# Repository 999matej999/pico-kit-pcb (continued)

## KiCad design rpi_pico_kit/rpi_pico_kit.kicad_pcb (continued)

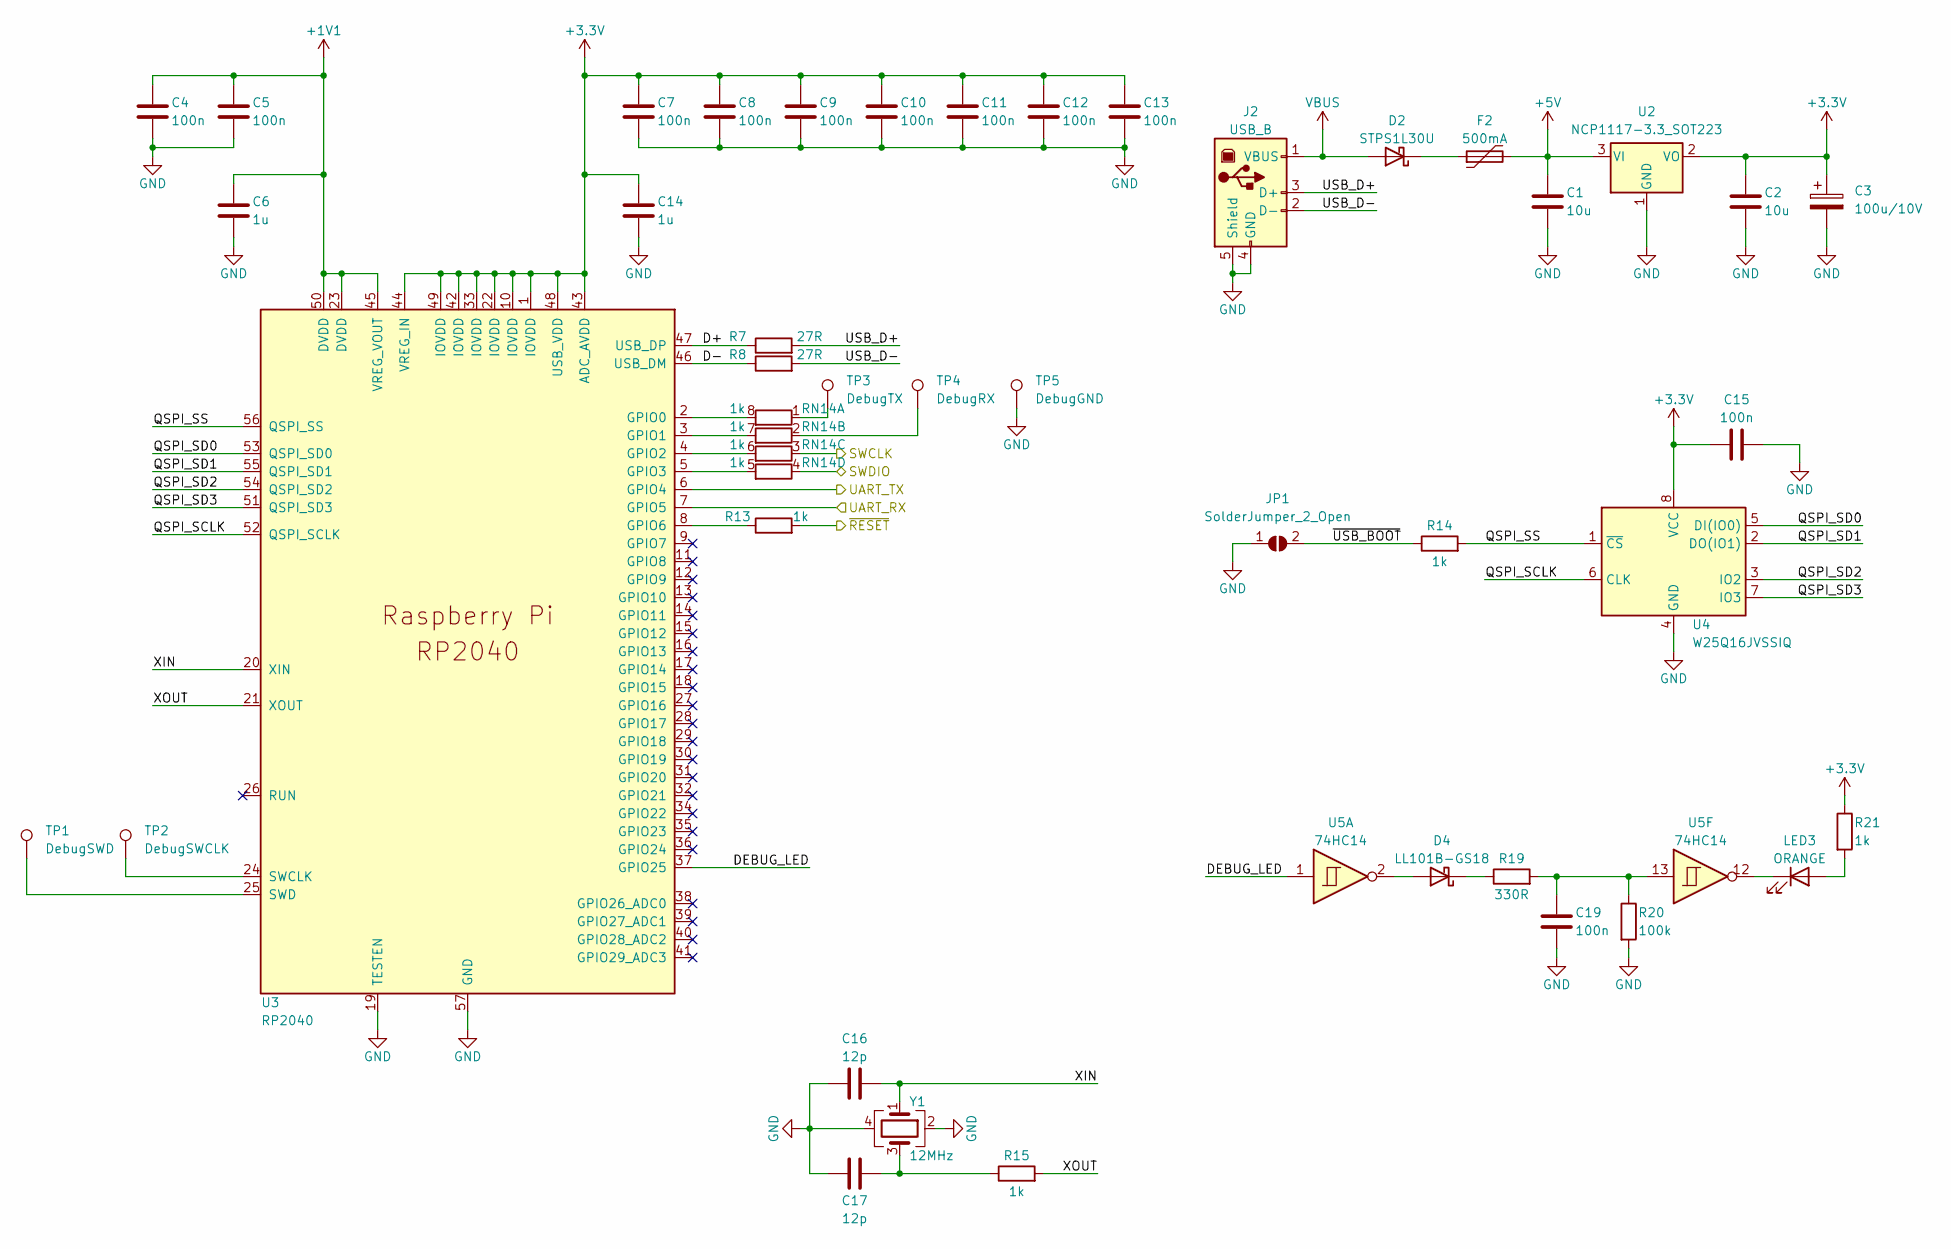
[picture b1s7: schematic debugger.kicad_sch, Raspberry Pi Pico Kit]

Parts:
C1, C2: 10u; C_0805_2012Metric_Pad1.18x1.45mm_HandSolder; Manufacturer Part Number CL21A106KOQNNNG
C3: 100u/10V; C_Elec_5x5.4; Manufacturer Part Number UWR1A101MCL1GB
C4, C5, C7, C8, C9, C10, C11, C12, C13, C15, C19: 100n; C_0603_1608Metric_Pad1.08x0.95mm_HandSolder; Manufacturer Part Number C0805C104M3RAC7800
C6, C14: 1u; C_0805_2012Metric_Pad1.18x1.45mm_HandSolder; Manufacturer Part Number C0805C105Z4VAC7800
C16, C17: 12p; C_0603_1608Metric_Pad1.08x0.95mm_HandSolder; Manufacturer Part Number C0805C120J1HAC7800
D2: STPS1L30U; D_SMB; Manufacturer Part Number STPS1L30U
D4: LL101B-GS18; D_MiniMELF; Manufacturer Part Number LL101B-GS18
F2: 500mA; Fuse_1206_3216Metric_Pad1.42x1.75mm_HandSolder; Manufacturer Part Number 0ZCJ0050FF2G
J2: USB_B; USB_B_Lumberg_2411_02_Horizontal; Manufacturer Part Number USB-B1HSW6
JP1: SolderJumper_2_Open; SolderJumper-2_P1.3mm_Open_RoundedPad1.0x1.5mm
LED3: ORANGE; LED_0805_2012Metric_Pad1.15x1.40mm_HandSolder; Manufacturer Part Number LTST-C170KFKT
R7, R8: 27R; R_0603_1608Metric_Pad0.98x0.95mm_HandSolder; Manufacturer Part Number RC0805FR-0727RL
R13, R14, R15, R21: 1k; R_0603_1608Metric_Pad0.98x0.95mm_HandSolder; Manufacturer Part Number RC0805FR-071KL
R19: 330R; R_0603_1608Metric_Pad0.98x0.95mm_HandSolder; Manufacturer Part Number RC0805FR-13330RL
R20: 100k; R_0603_1608Metric_Pad0.98x0.95mm_HandSolder; Manufacturer Part Number RC0805FR-07100KL
RN14: 1k; R_Array_Convex_4x0603
TP1: DebugSWD; TestPoint_Pad_D1.0mm
TP2: DebugSWCLK; TestPoint_Pad_D1.0mm
TP3: DebugTX; TestPoint_Pad_D1.0mm
TP4: DebugRX; TestPoint_Pad_D1.0mm
TP5: DebugGND; TestPoint_Pad_D1.0mm
U2: NCP1117-3.3_SOT223; SOT-223-3_TabPin2; Manufacturer Part Number NCP1117ST33T3G
U3: RP2040; RP2040-QFN-56; Manufacturer Part Number SC0914(13)
U4: W25Q16JVSSIQ; SOIC-8_5.275x5.275mm_P1.27mm; Manufacturer Part Number W25Q16JVSSIQ
U5: 74HC14; SOIC-14_3.9x8.7mm_P1.27mm; Manufacturer Part Number 74HC14S14-13
Y1: 12MHz; Crystal_SMD_0603-4Pin_6.0x3.5mm; Manufacturer Part Number ABM3B-12.000MHZ-10-1-U-T

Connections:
+1V1: C4.2, C5.2, C6.2, U3.23 (DVDD), U3.45 (VREG_VOUT), U3.50 (DVDD)
+3V3: C2.2, C3.1, C7.2, C8.2, C9.2, C10.2, C11.2, C12.2, C13.2, C14.2, C15.1, R21.1, U2.2 (VO), U3.1 (IOVDD), U3.10 (IOVDD), U3.22 (IOVDD), U3.33 (IOVDD), U3.42 (IOVDD), U3.43 (ADC_AVDD), U3.44 (VREG_IN), U3.48 (USB_VDD), U3.49 (IOVDD), U4.8 (VCC); also elsewhere on the board
+5V: C1.2, F2.2, U2.3 (VI); also elsewhere on the board
/DEBUGGER_RX: U3.6 (GPIO4); also elsewhere on the board
/DEBUGGER_TX: U3.7 (GPIO5); also elsewhere on the board
/Debugger/D+: R7.1, U3.47 (USB_DP)
/Debugger/D-: R8.1, U3.46 (USB_DM)
/Debugger/DEBUG_LED: U3.37 (GPIO25), U5.1
/Debugger/QSPI_SCLK: U3.52 (QSPI_SCLK), U4.6 (CLK)
/Debugger/QSPI_SD0: U3.53 (QSPI_SD0), U4.5 (DI(IO0))
/Debugger/QSPI_SD1: U3.55 (QSPI_SD1), U4.2 (DO(IO1))
/Debugger/QSPI_SD2: U3.54 (QSPI_SD2), U4.3 (IO2)
/Debugger/QSPI_SD3: U3.51 (QSPI_SD3), U4.7 (IO3)
/Debugger/QSPI_SS: R14.2, U3.56 (QSPI_SS), U4.1 (~CS)
/Debugger/USB_D+: J2.3 (D+), R7.2
/Debugger/USB_D-: J2.2 (D-), R8.2
/Debugger/XIN: C16.2, U3.20 (XIN), Y1.1
/Debugger/XOUT: R15.2, U3.21 (XOUT)
/Debugger/~USB_BOOT: JP1.2 (B), R14.1
/SWCLK: RN14.3 (R3.1); also elsewhere on the board
/SWDIO: RN14.4 (R4.1); also elsewhere on the board
/~RESET: R13.2; also elsewhere on the board
GND: C1.1, C2.1, C3.2, C4.1, C5.1, C6.1, C7.1, C8.1, C9.1, C10.1, C11.1, C12.1, C13.1, C14.1, C15.2, C16.1, C17.1, C19.1, J2.4 (GND), J2.5 (Shield), JP1.1 (A), R20.2, TP5.1, U2.1 (GND), U3.19 (TESTEN), U3.57 (GND), U4.4 (GND), Y1.2, Y1.4; also elsewhere on the board
unnamed: C17.2, R15.1, Y1.3
unnamed: C19.2, R19.2, R20.1, U5.13
unnamed: D2.1 (K), F2.1
unnamed: D4.2 (A), U5.2
unnamed: D4.1 (K), R19.1
unnamed: LED3.2 (A), R21.2
unnamed: LED3.1 (K), U5.12
unnamed: RN14.1 (R1.1), TP3.1
unnamed: RN14.8 (R1.2), U3.2 (GPIO0)
unnamed: RN14.2 (R2.1), TP4.1
unnamed: RN14.7 (R2.2), U3.3 (GPIO1)
unnamed: RN14.6 (R3.2), U3.4 (GPIO2)
unnamed: RN14.5 (R4.2), U3.5 (GPIO3)
unnamed: R13.1, U3.8 (GPIO6)
unnamed: TP2.1, U3.24 (SWCLK)
unnamed: TP1.1, U3.25 (SWD)
VBUS: D2.2 (A), J2.1 (VBUS)

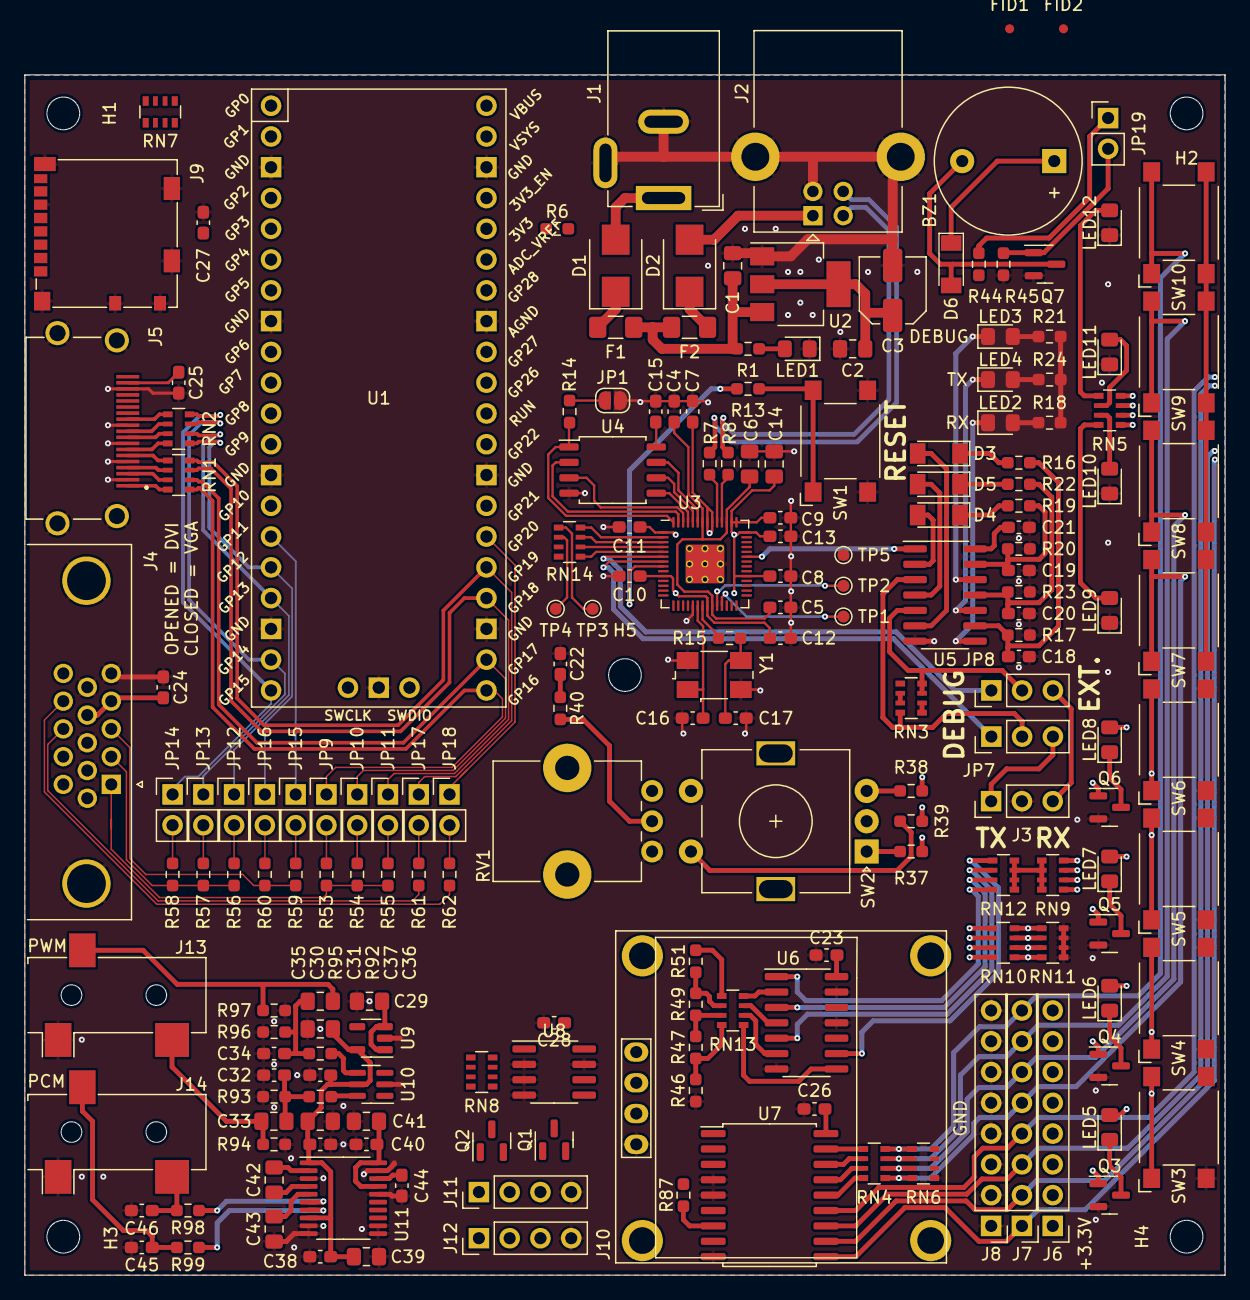
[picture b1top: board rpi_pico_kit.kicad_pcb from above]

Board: 4 copper layers, 99.1 x 99.1 mm, 196 parts (0 on the bottom side), 175 nets.

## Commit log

2022-01-17 added .gitignore file
2022-01-17 added kicad v6 project
2022-01-17 added second rpi pico as debugger
2022-01-17 added pinout for rpi pico
2022-01-17 added kit pinout
2022-01-17 added another components to schematic
2022-01-18 little changes
2022-01-18 moved dac buttons to hierarchical sheet
2022-01-18 removed dac buttons
2022-01-18 added SPI devices
2022-01-18 added i2c and audio interface
2022-01-18 added leds for uart, little changes
2022-01-18 edited debugger
2022-01-18 edited debugger, little changes
2022-01-18 edited pinout
2022-01-18 renamed parts, added footprints
2022-01-23 little changes, added EEPROM
2022-01-23 added jumper for 74165's MISO pin
2022-02-28 updated kicad version from 20211123 to 20220126
2022-03-06 added i2c interface for vga and dvi
2022-03-06 added uart selector
2022-03-06 added some footprints
2022-03-06 added dac buttons
2022-03-07 replaced spi expander
2022-03-07 replaced buttons in schematic
2022-03-07 added resistors to expander's buttons
2022-03-07 added i2c level shifters
2022-03-12 connected unused logic gates to ground
2022-03-16 added bypass capacitor to schmitt inverter
2022-03-17 changed schematic for uart leds
2022-03-18 added jumpers to vga
2022-03-18 changed pinout
2022-03-18 changed transistors to unused gates of 7414
2022-03-18 added test pads for uart and swd of debugger
2022-03-18 changed encoder button pull-up to pull-down
2022-03-18 added some MPNs, added fiducials
2022-03-19 edited 5V I2C, added some footprints, MPNs, added HDMI footprint library
2022-03-19 added some footprints and MPNs
2022-03-19 added MPNs for capacitors
2022-03-19 added MPNs for resistors
2022-03-19 added another MPNs, edited color of LEDs
2022-03-19 added monostable for debug led
2022-03-19 changed back 7414 gates to mosfets
2022-03-19 added missing MPNs to edited parts
2022-03-19 changed name of LEDs from D to LED
2022-03-19 added MPNs
2022-03-19 added micro sd footprint and MPN
2022-03-19 added protective diode to buzzer
2022-03-19 added SSD1306 library
2022-03-19 migrated library SSD1306, added footprint
2022-03-19 changed numbering of parts
2022-03-20 added solder jumpers to swd, changed numbering of parts
2022-03-20 changed uart pin headers to jumpers
2022-03-20 added PTC fuses
2022-03-20 added empty pcb file
2022-03-20 added parts to pcb
2022-03-20 added some 3D models
2022-03-20 changed switches from tht to smd
2022-03-20 changed footprint for tactile switches, added 3D model
2022-03-20 changed tactile switch 3D model
2022-03-20 added 3D models, repaired SSD1306 footprint
2022-03-20 added sim card 3D model
2022-03-20 changed footprint for flash memory
2022-03-20 added USB B 3D model
2022-03-20 changed footprint for crystal
2022-03-20 added OLED socket
2022-03-20 added RPi Pico socket
2022-03-20 repaired switch 3D model
2022-03-21 added JumperTHT library
2022-03-21 renamed files of JumperTHT library
2022-03-21 changed footprint for THT jumpers to use jumper 3D model
2022-03-21 changed RV1 3D model
2022-03-21 changed potentiometer footprint
2022-03-21 edited board setup
2022-03-21 edited mask clearance
2022-03-21 created Custom library with custom SMD button switch
2022-03-21 updated kicad version from 20220211 to 20220308
2022-03-21 edited OLED footprint
2022-03-21 removed additional holes for oled
2022-03-21 initial changes in pcb, drawn pcb outline
2022-03-21 filtered controls and indicators
2022-03-21 changed position of controls and indicators
2022-03-21 added rpi pico THT and SMD footprint
2022-03-21 edited RPi Pico SMD and THT footprint
2022-03-21 edited RPi Pico THT library
2022-03-21 changed rpi pico footprint in project
2022-03-21 pcb changes
2022-03-22 changed resistors to resistor arrays
2022-03-22 added footprints for resistor arrays
2022-03-22 added missing footprints
2022-03-22 downgraded kicad version from 20220308 to 20220211
2022-03-22 added resistor arrays to pcb
2022-03-22 changed footprints from 0805 to 0603
2022-03-22 changed footprint U10
2022-03-22 SPI conflict solved
2022-03-22 changed footprint for diodes
2022-03-22 rearranged parts to blocks
2022-03-22 added RPi Pico THT socket footprint
2022-03-22 added RPi Pico THT socket 3D model
2022-03-22 changed RPi Pico footprint in pcb
2022-03-22 changed footprints for resistor arrays
2022-03-22 added names to differential pairs
2022-03-22 updated pcb netlist
2022-03-22 added net classes
2022-03-24 replaced audio
2022-03-24 4 layer stackup
2022-03-24 edited layer thickness
2022-03-25 added permitivity of JLC 7628 stackup
2022-03-25 edited thickness of prepregs layers
2022-03-25 added differential dvi lines (unrouted 523)
2022-03-25 edited impedance controller tracks parameters (unrouted 534)
2022-03-25 added GND filed zones (unrouted 421)
2022-03-25 added nets to vga class
2022-03-25 vga (unrouted 401)
2022-03-25 vga (unrouted 389)
2022-03-25 updated GND plane
2022-03-25 moved text
2022-03-25 changed eeprom I2C address from 0x50 to 0x51
2022-03-26 solved some DRC errors
2022-03-26 audio (unrouted 353)
2022-03-26 added GND vias to audio
2022-03-26 spi (unrouted 319)
2022-03-26 edited VGA tracks width
2022-03-26 basic leds (unrouted 295)
2022-03-26 dac buttons (unrouted 270)
2022-03-26 updated GND plane (unrouted 262)
2022-03-26 potentiomete, encoder (unrouted 257)
2022-03-26 expander (unrouted 234)
2022-03-26 added 5th hole at the center
2022-03-27 buzzer (unrouted 226)
2022-03-27 power (unrouted 221)
2022-03-27 power (unrouted 209)
2022-03-27 moved debugger (unrouted 190)
2022-03-27 debugger (unrouted 171)
2022-03-27 debugger (unrouted 163)
2022-03-27 debugger (unrouted 159)
2022-03-27 crystal (unrouted 155)
2022-03-27 little changes (unrouted 153)
2022-03-27 reset, test pads (unrouted 139)
2022-03-27 monostable (unrouted 136)
2022-03-27 monostable
2022-03-27 monostable (unrouted 115)
2022-03-27 monostable (unrouted 112)
2022-03-27 monostable (unrouted 105)
2022-03-27 little changes (unrouted 104)
2022-03-28 solved some errors and warnings
2022-03-28 monostable leds (unrouted 99)
2022-03-28 monostable leds (unrouted 96)
2022-03-28 updated GND plane, added GND vias
2022-03-28 edited references
2022-03-28 fiducials
2022-03-28 sd card (unrouted 92)
2022-03-28 sd card (unrouted 87)
2022-03-28 i2c (unrouted 74)
2022-03-28 little changes (unrouted 73)
2022-03-28 3V3 supply (unrouted 39)
2022-03-28 5V supply (unrouted 35)
2022-03-28 i2c, swd (unrouted 27)
2022-03-28 i2c (unrouted 25)
2022-03-28 little changes (unrouted 21)
2022-03-29 schematic cleared annotation
2022-03-29 renumbered parts
2022-03-29 renumbered pwr
2022-03-29 renumbered pcb
2022-03-29 repaired error
2022-03-29 solved some drc errors and warnings
2022-03-29 added some description
2022-03-29 added dc jack polarity symbol
2022-03-29 edited dc jack symbol
2022-03-29 changed resistor value
2022-03-29 changed dimensions of pcb to 10x10cm
2022-03-29 greater polygon
2022-03-29 changed SN polygon
2022-03-29 sd card, i2c (unrouted 14)
2022-03-29 encoder, uart (unrouted 10)
2022-03-29 another connections to pico (unrouted 5)
2022-03-29 unrouted 0 !!!!!!!!
2022-03-29 leds (unrouted 3)
2022-03-30 added GND vias
2022-03-30 repaired vias
2022-03-30 resolved some warnings
2022-03-30 added board dimensions
2022-03-30 edited title block
2022-03-30 added some MPNs
2022-03-30 changed potentiometer MPN
2022-03-30 updated MPNs in pcb
2022-03-30 added gerber files
2022-03-30 added drill files
2022-03-30 added map files
2022-03-30 gerber settings
2022-03-30 changed polygon dimensions
2022-03-31 edited gerber files
2022-04-07 changed date and revision number
2022-04-07 visual changes in schematic
2022-04-11 added gerber data zip
2022-05-15 updated pinout name BUZZER-> PIEZO
2023-05-29 Create LICENSE
2023-05-29 added README
